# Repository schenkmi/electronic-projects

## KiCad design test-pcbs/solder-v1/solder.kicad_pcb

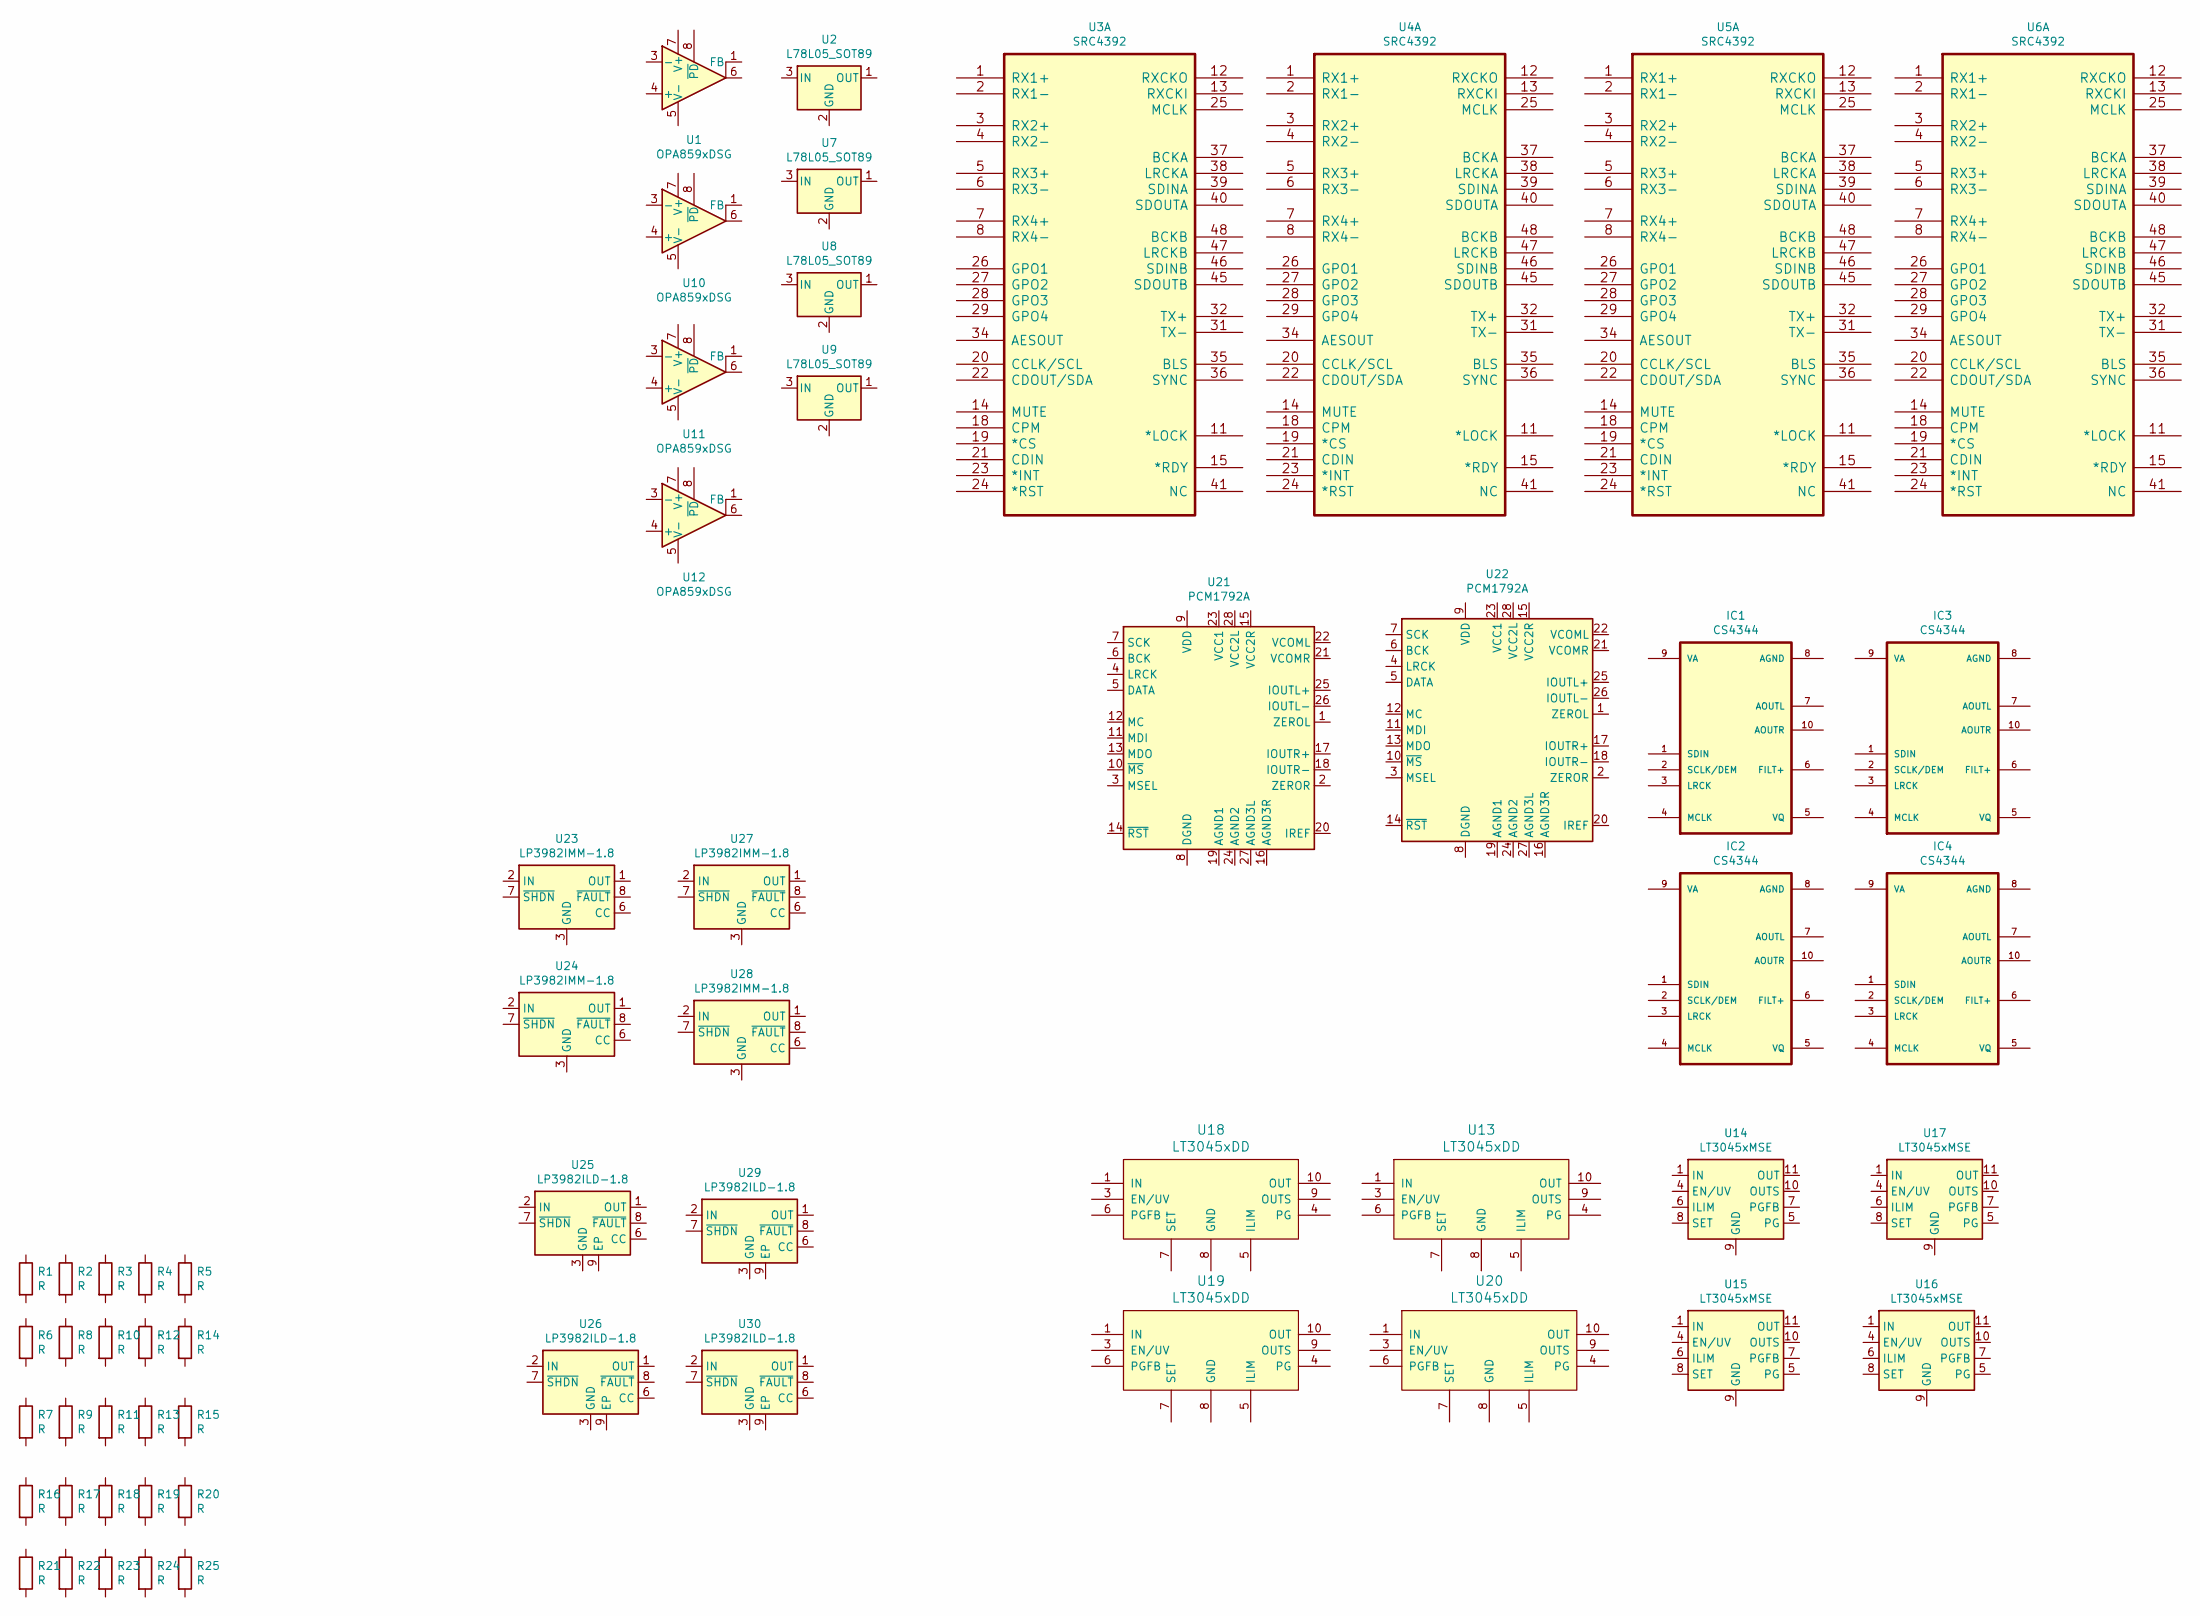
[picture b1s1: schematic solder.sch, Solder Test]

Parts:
IC1, IC2, IC3, IC4: CS4344; TSSOP-10_3x3mm_P0.5mm; MPN CS4344-DZZ
R1, R2, R3, R4, R5: R; R_0805_2012Metric_Pad1.20x1.40mm_HandSolder
R6, R8, R10, R12, R14: R; R_0603_1608Metric_Pad0.98x0.95mm_HandSolder
R7, R9, R11, R13, R15: R; R_0603_1608Metric
R16, R17, R18, R19, R20: R; R_0402_1005Metric_Pad0.72x0.64mm_HandSolder
R21, R22, R23, R24, R25: R; R_0402_1005Metric
U1, U10, U11, U12: OPA859xDSG; WSON-8-1EP_2x2mm_P0.5mm_EP0.9x1.6mm
U2, U7, U8, U9: L78L05_SOT89; SOT-89-3
U3, U4, U5, U6: SRC4392; TQFP-48_7x7mm_P0.5mm
U13, U18, U19, U20: LT3045xDD; DFN-10-1EP_3x3mm_P0.5mm_EP1.55x2.48mm
U14, U15, U16, U17: LT3045xMSE; MSOP-12-1EP_3x4mm_P0.65mm_EP1.65x2.85mm
U21, U22: PCM1792A; SSOP-28_5.3x10.2mm_P0.65mm
U23, U24, U27, U28: LP3982IMM-1.8; VSSOP-8_3.0x3.0mm_P0.65mm
U25, U26, U29, U30: LP3982ILD-1.8; WSON-8-1EP_3x2.5mm_P0.5mm_EP1.2x1.5mm_PullBack_ThermalVias

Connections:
unnamed: U1.5 (V-), U1.9 (V-)
unnamed: U10.5 (V-), U10.9 (V-)
unnamed: U11.5 (V-), U11.9 (V-)
unnamed: U12.5 (V-), U12.9 (V-)
unnamed: U13.1 (IN), U13.2 (IN)
unnamed: U13.8 (GND), U13.11 (GND)
unnamed: U14.1 (IN), U14.2 (IN), U14.3 (IN)
unnamed: U14.11 (OUT), U14.12 (OUT)
unnamed: U14.9 (GND), U14.13 (GND)
unnamed: U15.1 (IN), U15.2 (IN), U15.3 (IN)
unnamed: U15.11 (OUT), U15.12 (OUT)
unnamed: U15.9 (GND), U15.13 (GND)
unnamed: U16.1 (IN), U16.2 (IN), U16.3 (IN)
unnamed: U16.11 (OUT), U16.12 (OUT)
unnamed: U16.9 (GND), U16.13 (GND)
unnamed: U17.1 (IN), U17.2 (IN), U17.3 (IN)
unnamed: U17.11 (OUT), U17.12 (OUT)
unnamed: U17.9 (GND), U17.13 (GND)
unnamed: U18.1 (IN), U18.2 (IN)
unnamed: U18.8 (GND), U18.11 (GND)
unnamed: U19.1 (IN), U19.2 (IN)
unnamed: U19.8 (GND), U19.11 (GND)
unnamed: U20.1 (IN), U20.2 (IN)
unnamed: U20.8 (GND), U20.11 (GND)
unnamed: U23.1 (OUT), U23.4 (OUT)
unnamed: U24.1 (OUT), U24.4 (OUT)
unnamed: U25.1 (OUT), U25.4 (OUT)
unnamed: U26.1 (OUT), U26.4 (OUT)
unnamed: U27.1 (OUT), U27.4 (OUT)
unnamed: U28.1 (OUT), U28.4 (OUT)
unnamed: U29.1 (OUT), U29.4 (OUT)
unnamed: U30.1 (OUT), U30.4 (OUT)

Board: 2 copper layers, 59 parts (0 on the bottom side), 32 nets, no tracks yet.

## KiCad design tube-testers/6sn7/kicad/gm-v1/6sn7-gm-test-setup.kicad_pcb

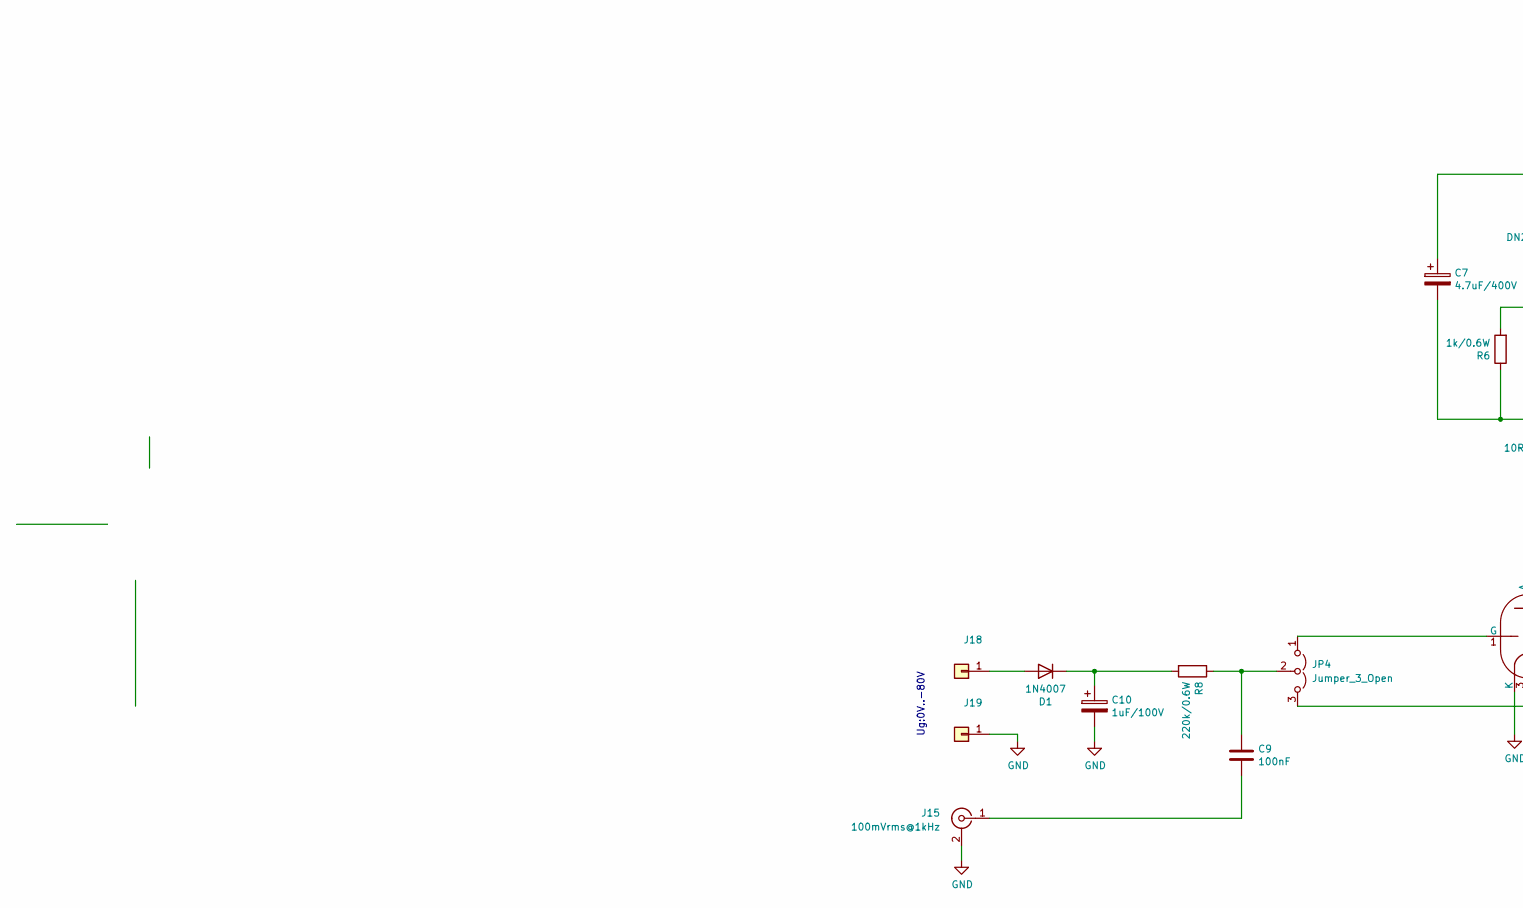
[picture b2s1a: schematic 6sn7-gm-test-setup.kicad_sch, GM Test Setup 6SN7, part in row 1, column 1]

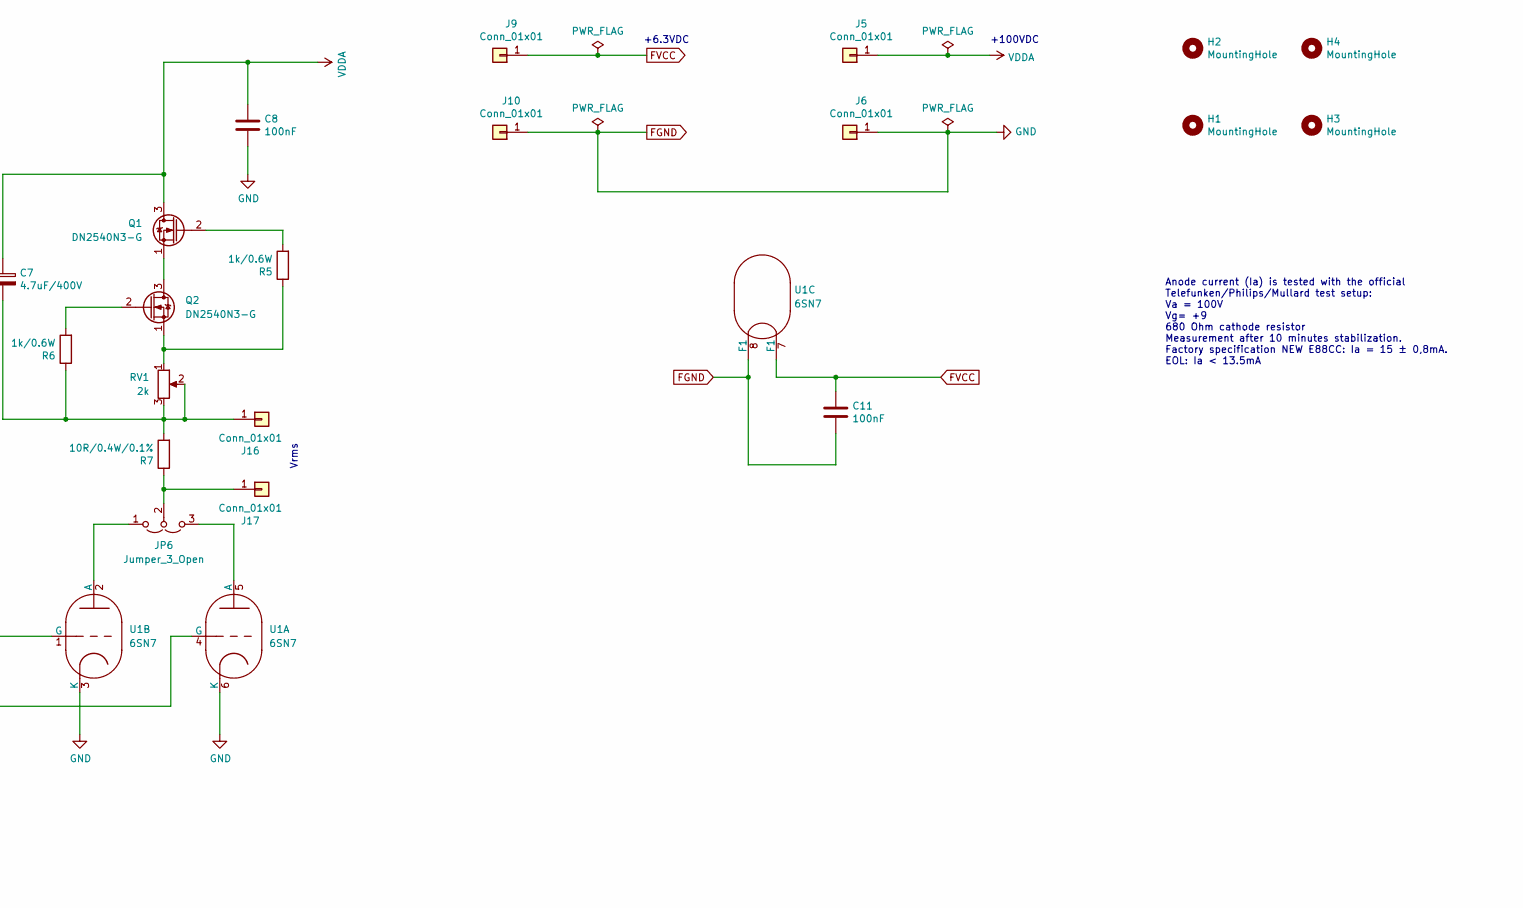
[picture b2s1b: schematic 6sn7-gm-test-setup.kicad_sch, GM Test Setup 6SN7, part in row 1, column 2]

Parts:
C7: 4.7uF/400V; CP_Radial_D10.0mm_P5.00mm
C8: 100nF; C_Rect_L16.5mm_W5.0mm_P15.00mm_MKT
C9, C11: 100nF; C_Rect_L7.2mm_W2.5mm_P5.00mm_FKS2_FKP2_MKS2_MKP2
C10: 1uF/100V; CP_Radial_D5.0mm_P2.00mm
D1: 1N4007; D_DO-41_SOD81_P10.16mm_Horizontal
H1, H2, H3, H4: MountingHole; MountingHole_3.2mm_M3_Pad_Via
J5, J6, J9, J10: Conn_01x01; Pin_D1.3mm_L11.0mm
J15: 100mVrms@1kHz; RCA-Phono_CUI-Devices_RCJ-02X_Vertical
J16, J17: Conn_01x01; Pin_D1.0mm_L10.0mm
J18, J19: Pin_D1.0mm_L10.0mm
JP4, JP6: Jumper_3_Open; PinHeader_1x03_P2.54mm_Vertical
Q1, Q2: DN2540N3-G; TO-92_Inline
R5, R6: 1k/0.6W; R_Axial_DIN0207_L6.3mm_D2.5mm_P10.16mm_Horizontal
R7: 10R/0.4W/0.1%; R_Axial_DIN0207_L6.3mm_D2.5mm_P10.16mm_Horizontal
R8: 220k/0.6W; R_Axial_DIN0207_L6.3mm_D2.5mm_P10.16mm_Horizontal
RV1: 2k; Potentiometer_Bourns_3296W_Vertical
U1: 6SN7; TubeOctal

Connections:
FGND: C8.2, C10.2, C11.2, J6.1, J10.1, J15.2 (Ext), J19.1, U1.3 (K), U1.6 (K), U1.8 (F1)
FVCC: C11.1, J9.1, U1.7 (F1)
unnamed: D1.2 (A), J18.1
unnamed: C10.1, D1.1 (K), R8.2
unnamed: C9.2, J15.1 (In)
unnamed: C7.2, J16.1, R6.1, R7.2, RV1.2, RV1.3
unnamed: J17.1, JP6.2 (C), R7.1
unnamed: JP4.1 (A), U1.1 (G)
unnamed: JP4.3 (B), U1.4 (G)
unnamed: C9.1, JP4.2 (C), R8.1
unnamed: JP6.1 (A), U1.2 (A)
unnamed: JP6.3 (B), U1.5 (A)
unnamed: Q1.2 (G), R5.2
unnamed: Q1.1 (S), Q2.3 (D)
unnamed: Q2.2 (G), R6.2
unnamed: Q2.1 (S), R5.1, RV1.1
VDDA: C7.1, C8.1, J5.1, Q1.3 (D)

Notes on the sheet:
+6.3VDC
Anode current (Ia) is tested with the official Telefunken/Philips/Mullard test setup: Va = 100V Vg= +9 680 Ohm cathode resistor Measurement after 10 minutes stabilization. Factory specification NEW E88CC: Ia = 15 ± 0,8mA. EOL: Ia < 13.5mA
+100VDC
Vrms
Ug:0V..-80V

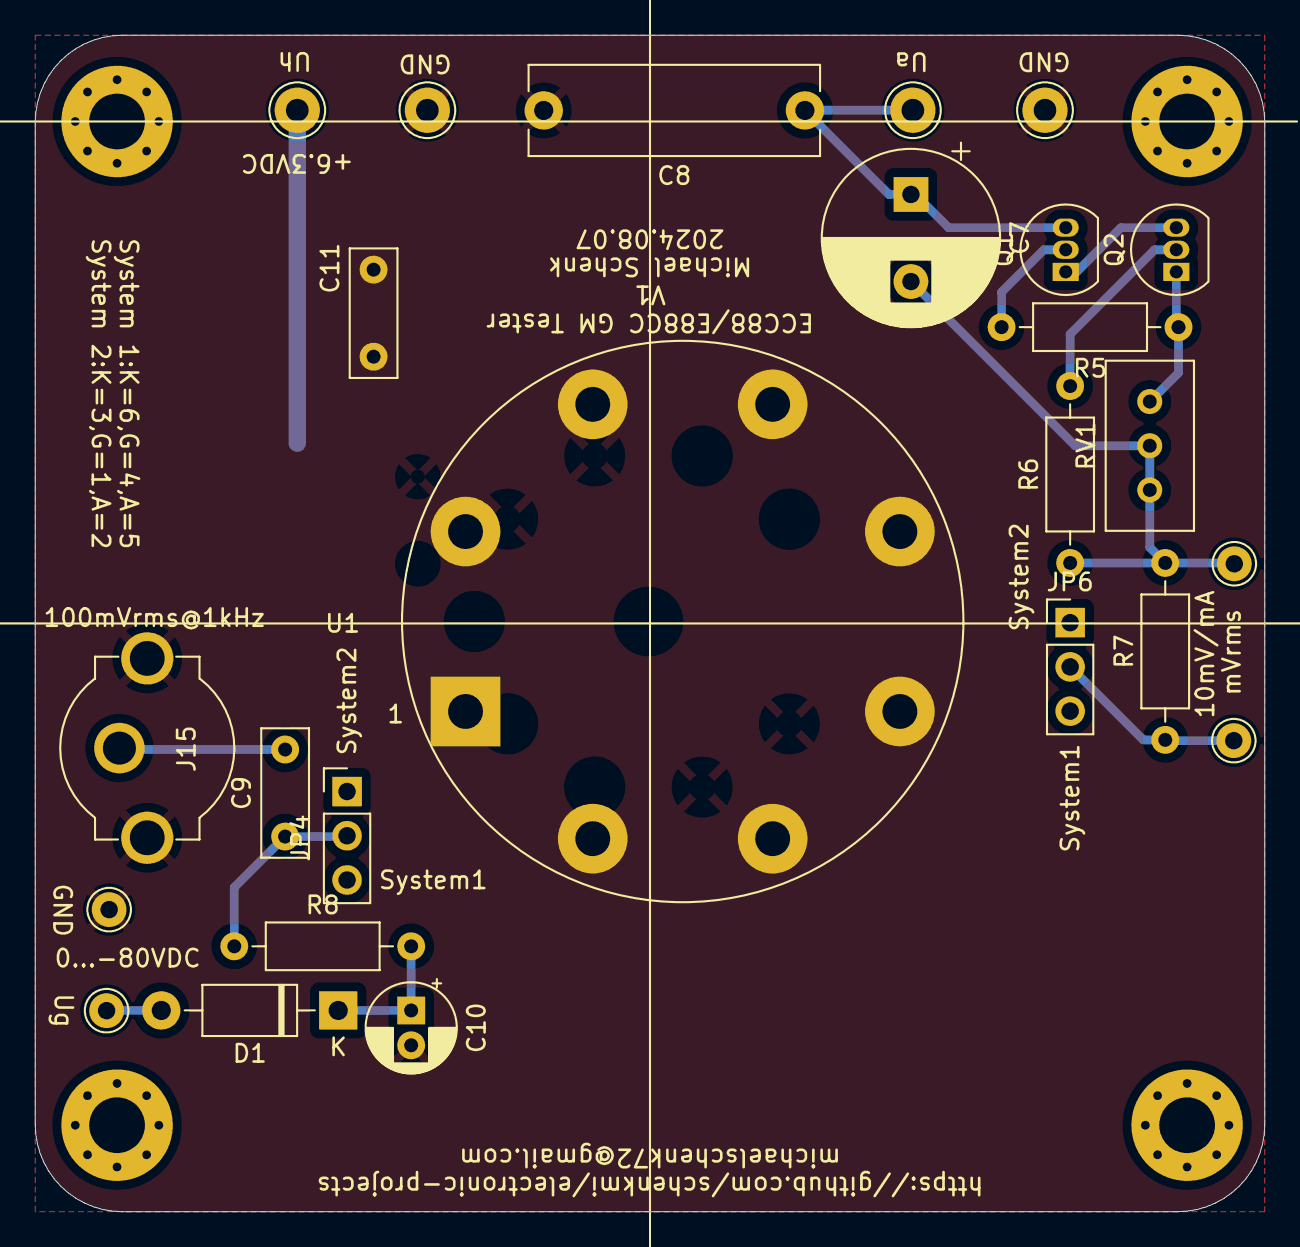
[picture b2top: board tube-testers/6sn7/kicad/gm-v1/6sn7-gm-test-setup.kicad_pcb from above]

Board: 2 copper layers, 70.6 x 67.6 mm, 29 parts (0 on the bottom side), 17 nets.

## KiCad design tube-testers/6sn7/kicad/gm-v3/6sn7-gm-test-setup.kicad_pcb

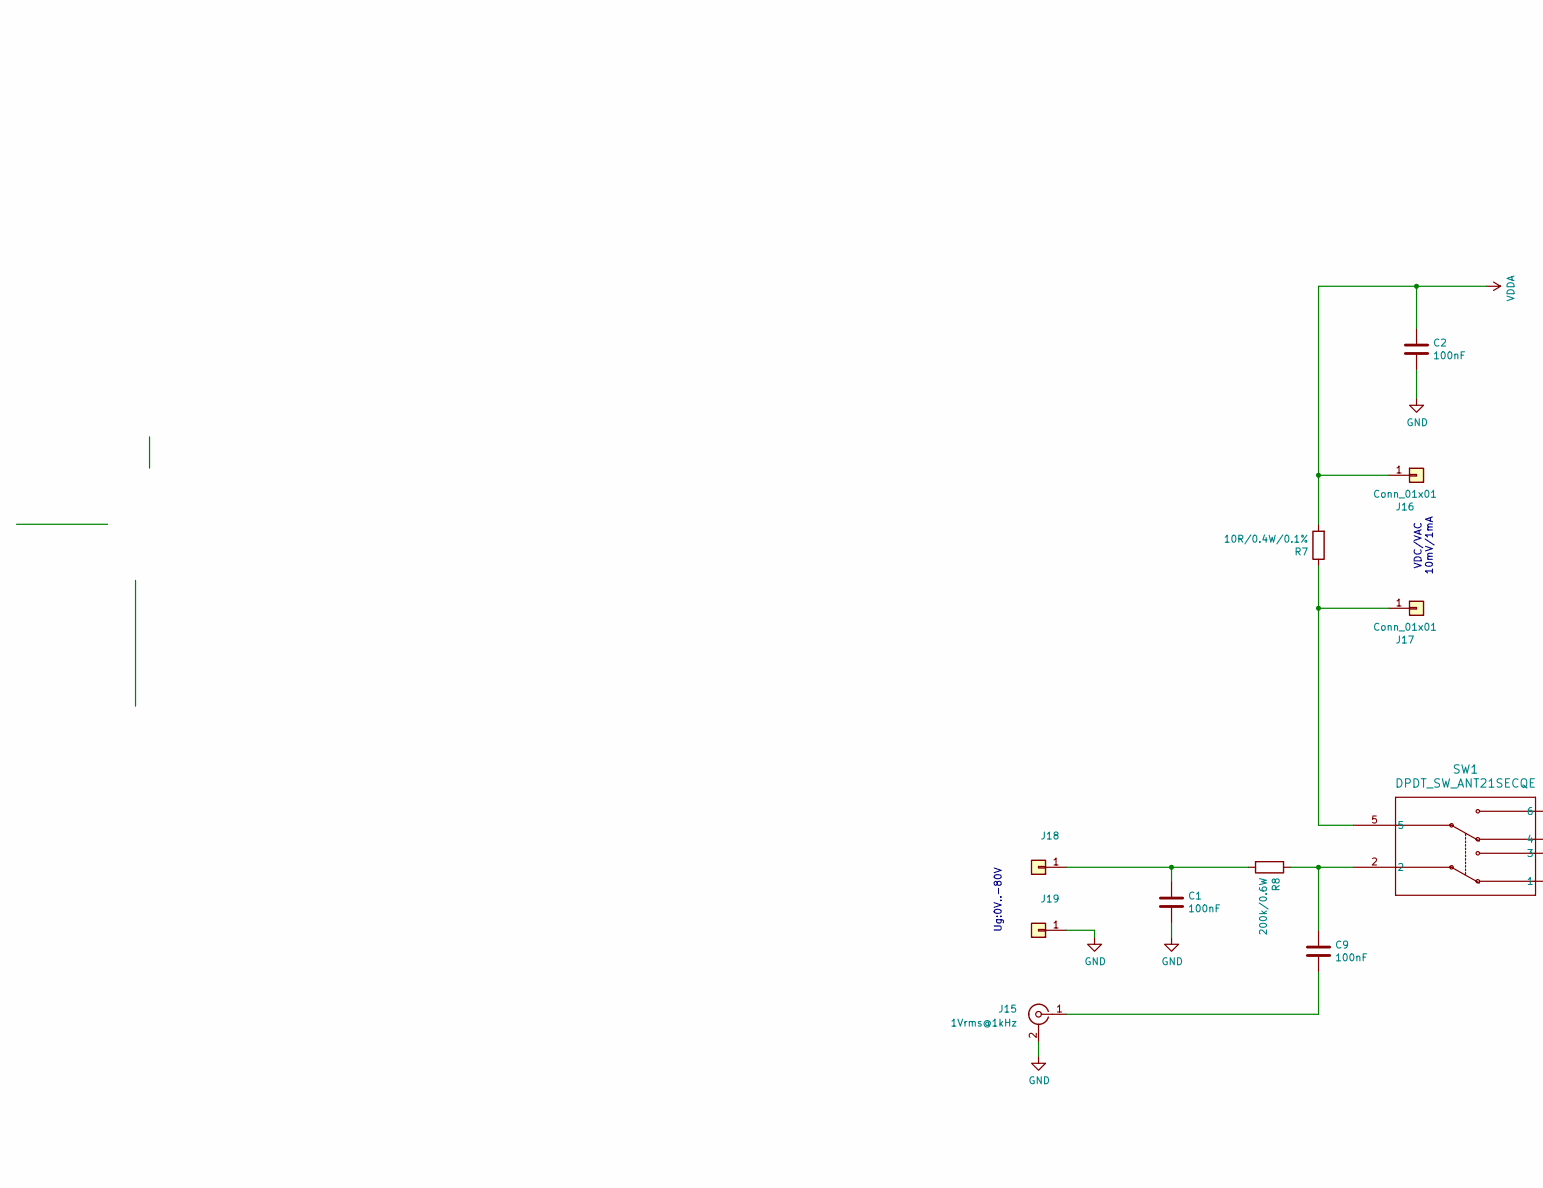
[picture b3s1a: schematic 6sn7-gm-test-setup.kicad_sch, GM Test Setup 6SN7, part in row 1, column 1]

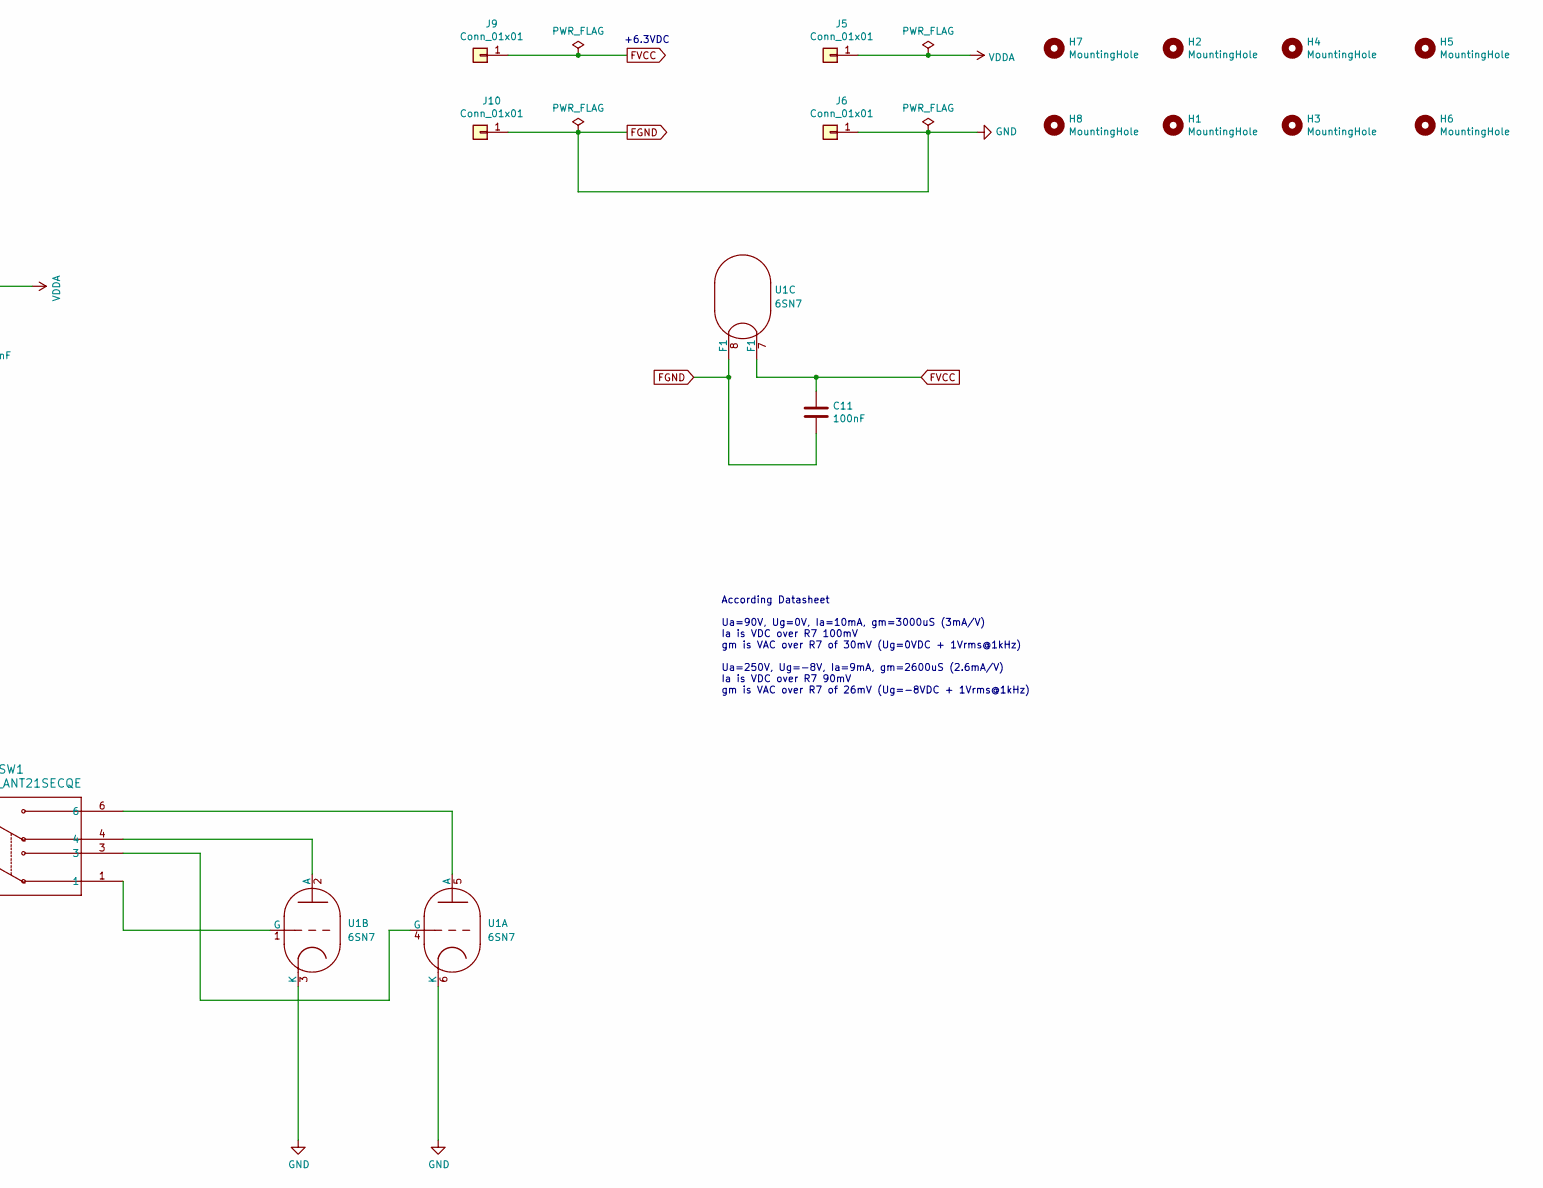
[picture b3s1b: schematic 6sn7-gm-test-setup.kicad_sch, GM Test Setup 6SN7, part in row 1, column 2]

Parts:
C1, C9, C11: 100nF; C_Rect_L7.2mm_W2.5mm_P5.00mm_FKS2_FKP2_MKS2_MKP2
C2: 100nF; C_Rect_L16.5mm_W5.0mm_P15.00mm_MKT
H1, H2, H3, H4, H5, H6, H7, H8: MountingHole; MountingHole_3.2mm_M3_Pad_Via
J5, J6, J9, J10: Conn_01x01; Pin_D1.3mm_L11.0mm
J15: 1Vrms@1kHz; RCA-Phono_CUI-Devices_RCJ-02X_Vertical
J16, J17: Conn_01x01; Pin_D1.0mm_L10.0mm
J18, J19: Pin_D1.0mm_L10.0mm
R7: 10R/0.4W/0.1%; R_Axial_DIN0207_L6.3mm_D2.5mm_P10.16mm_Horizontal
R8: 200k/0.6W; R_Axial_DIN0207_L6.3mm_D2.5mm_P10.16mm_Horizontal
SW1: DPDT_SW_ANT21SECQE; SW6_ANT21SECQE_CRS
U1: 6SN7; TubeOctal

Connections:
FGND: C1.2, C2.2, C11.2, J6.1, J10.1, J15.2 (Ext), J19.1, U1.3 (K), U1.6 (K), U1.8 (F1)
FVCC: C11.1, J9.1, U1.7 (F1)
unnamed: C9.1, R8.1, SW1.2
unnamed: C9.2, J15.1 (In)
unnamed: J17.1, R7.1, SW1.5
unnamed: C1.1, J18.1, R8.2
unnamed: SW1.6, U1.5 (A)
unnamed: SW1.3, U1.4 (G)
unnamed: SW1.4, U1.2 (A)
unnamed: SW1.1, U1.1 (G)
VDDA: C2.1, J5.1, J16.1, R7.2

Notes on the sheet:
+6.3VDC
VDC/VAC 10mV/1mA
Ug:0V..-80V
According Datasheet Ua=90V, Ug=0V, Ia=10mA, gm=3000uS (3mA/V) Ia is VDC over R7 100mV gm is VAC over R7 of 30mV (Ug=0VDC + 1Vrms@1kHz) Ua=250V, Ug=-8V, Ia=9mA, gm=2600uS (2.6mA/V) Ia is VDC over R7 90mV gm is VAC over R7 of 26mV (Ug=-8VDC + 1Vrms@1kHz)

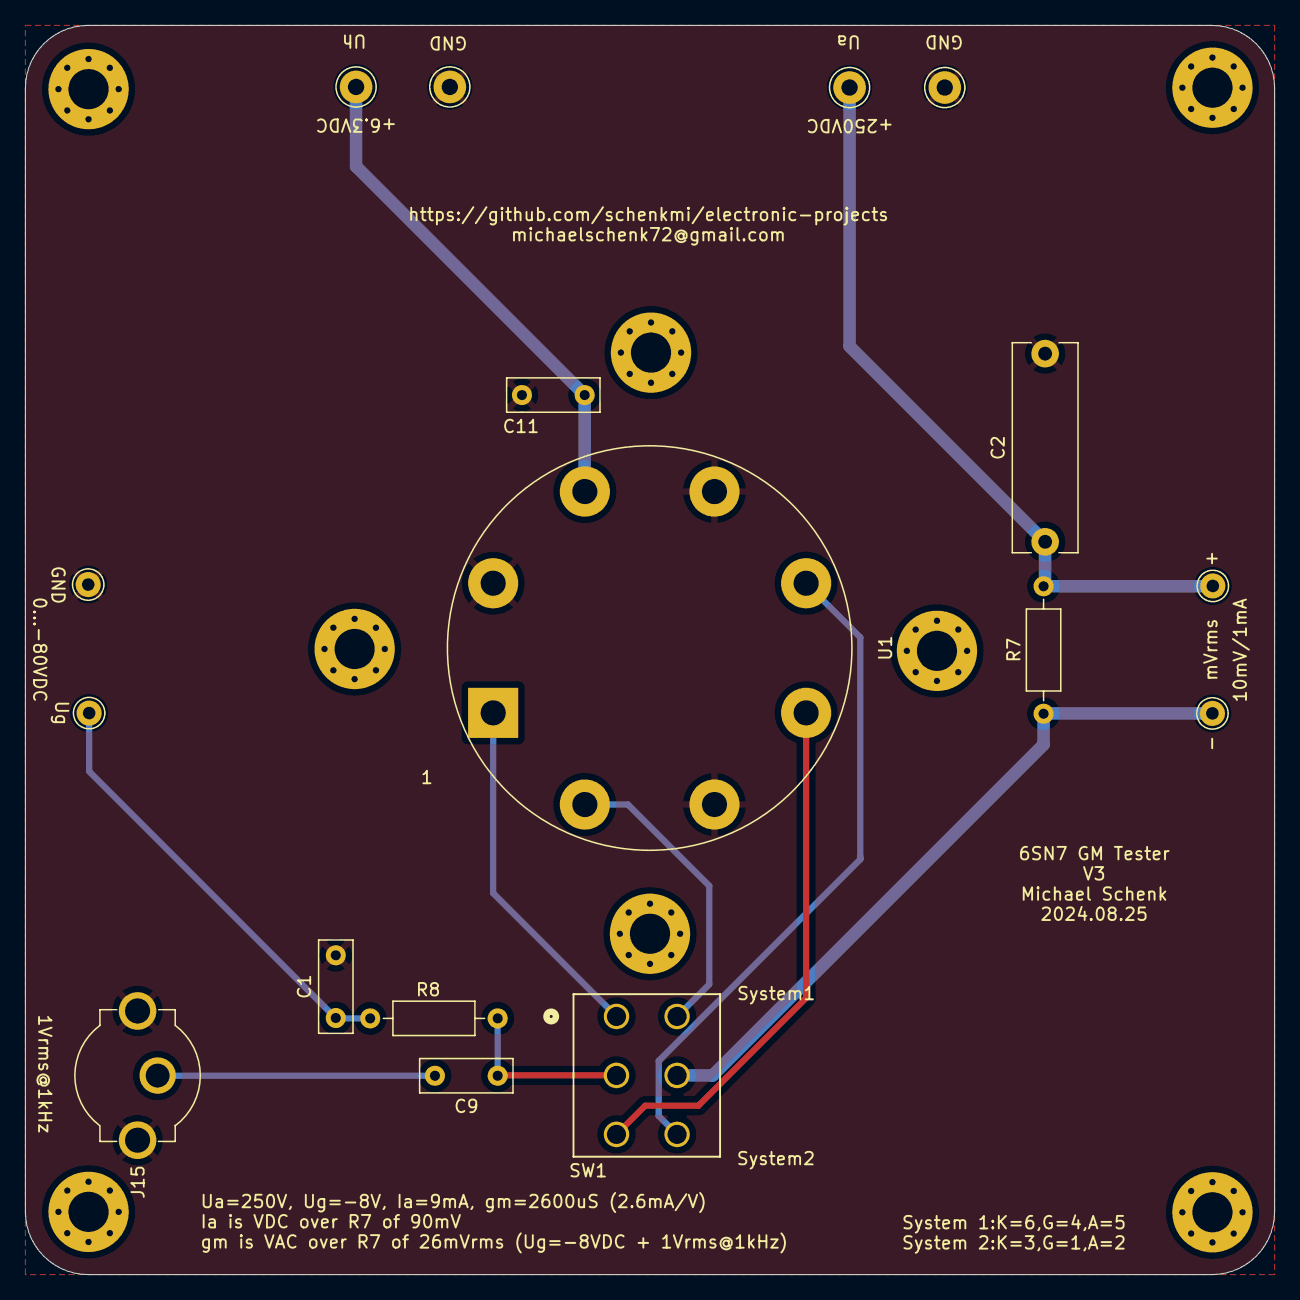
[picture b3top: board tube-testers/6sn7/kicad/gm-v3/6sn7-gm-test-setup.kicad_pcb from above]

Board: 2 copper layers, 99.6 x 99.6 mm, 25 parts (0 on the bottom side), 11 nets.

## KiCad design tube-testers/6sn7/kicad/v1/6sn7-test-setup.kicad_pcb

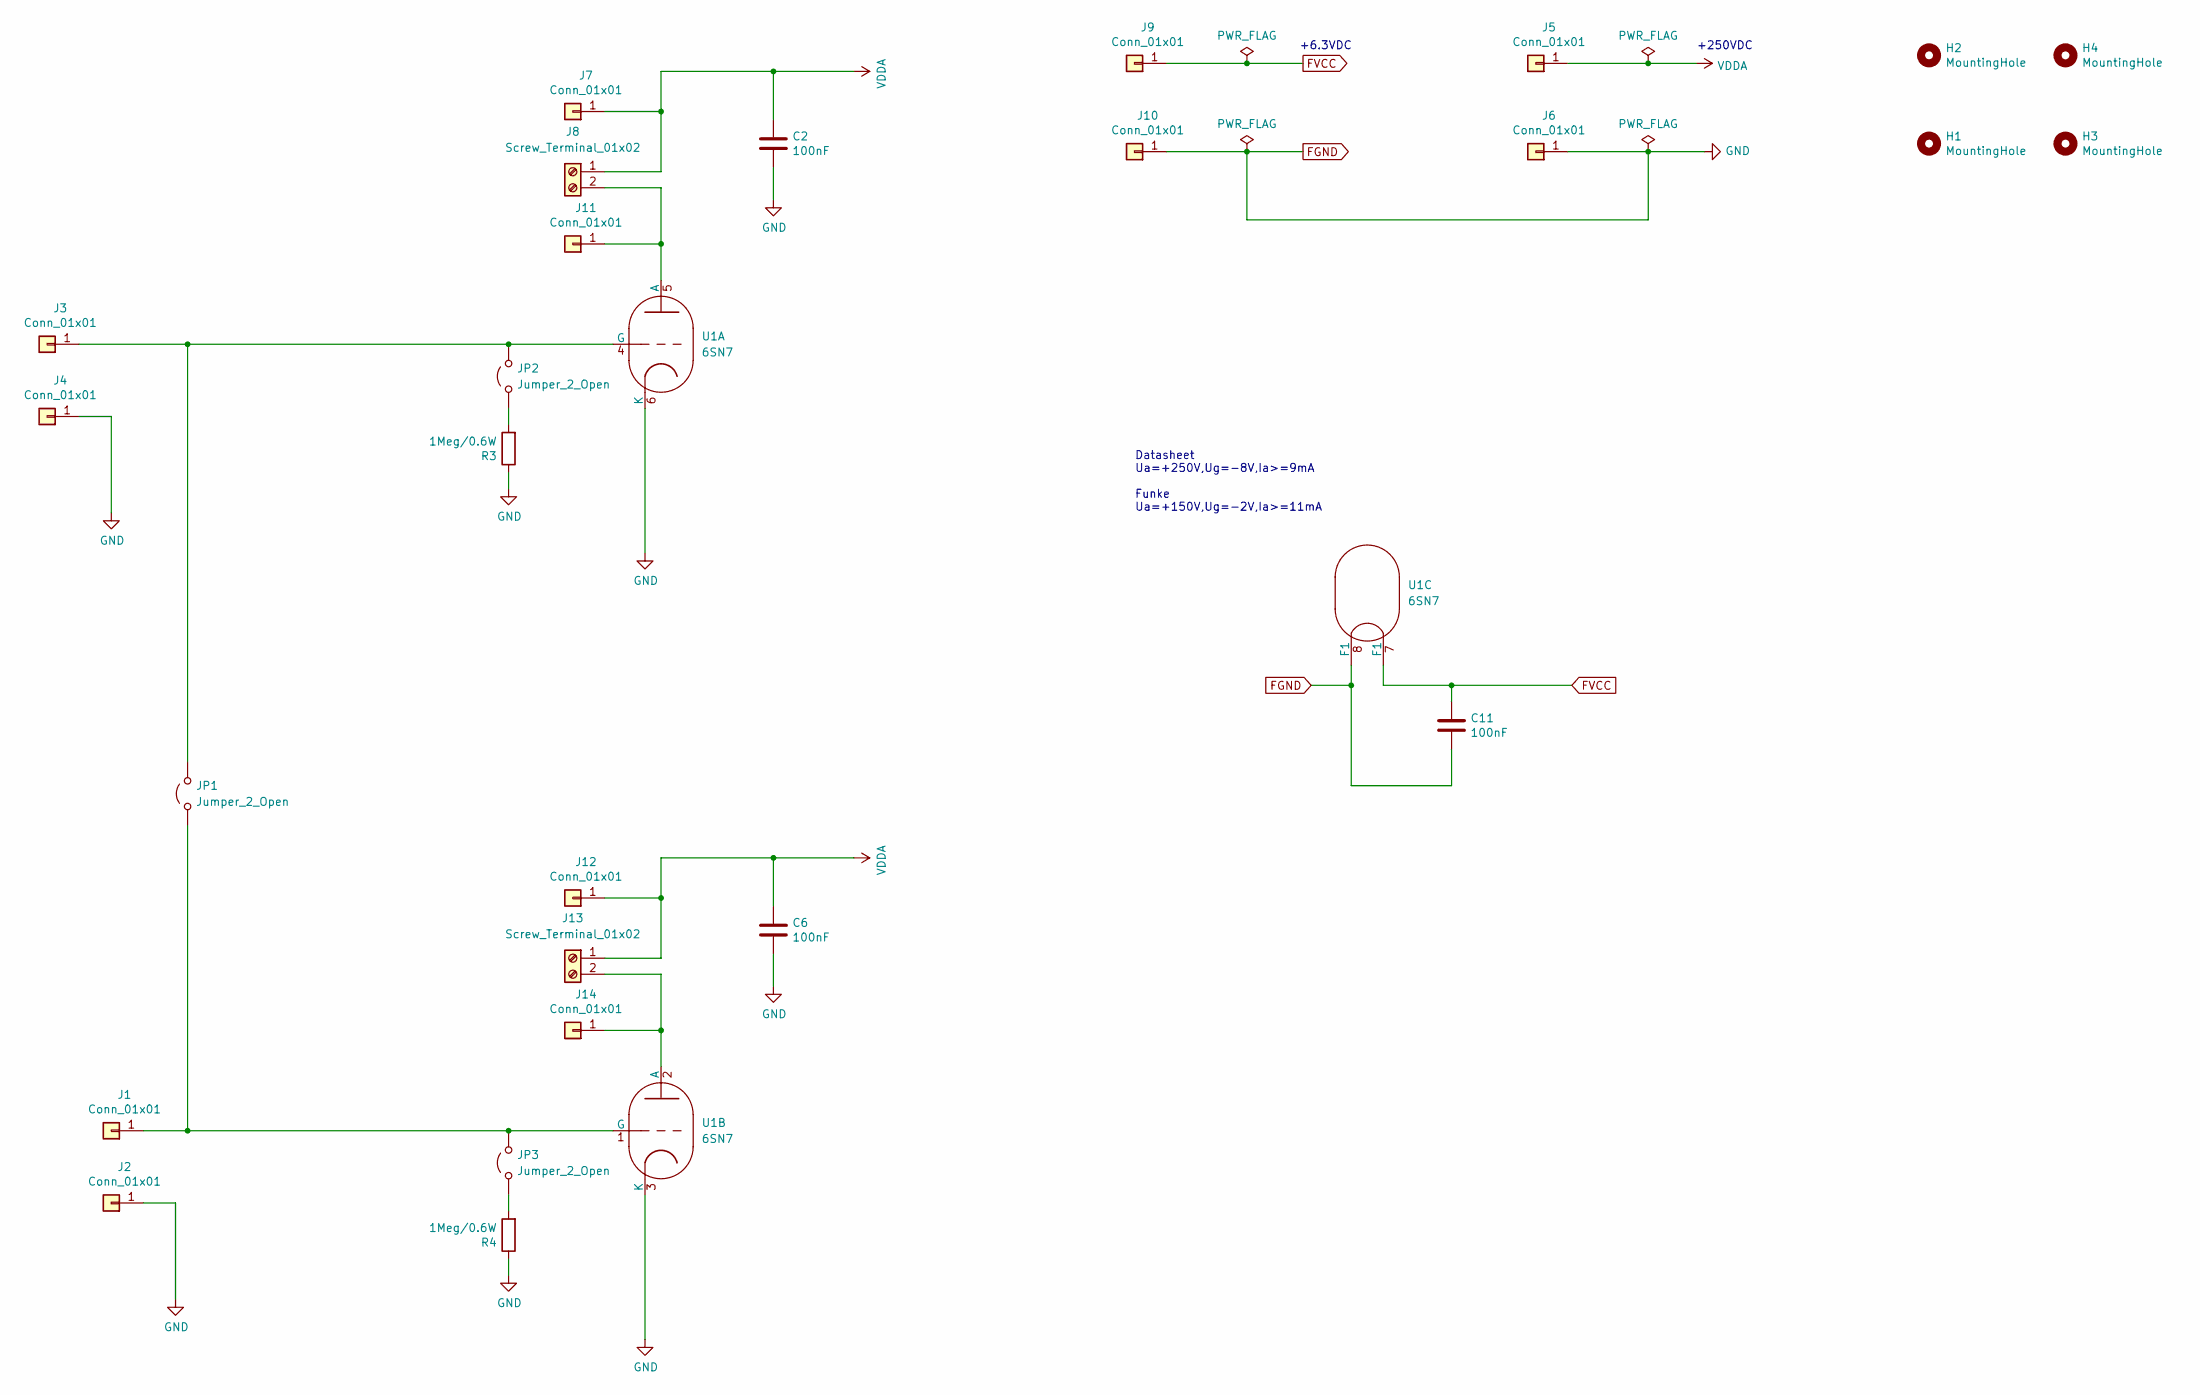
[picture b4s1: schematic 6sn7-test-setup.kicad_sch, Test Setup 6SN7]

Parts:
C2, C6: 100nF; C_Rect_L16.5mm_W5.0mm_P15.00mm_MKT
C11: 100nF; C_Rect_L7.2mm_W2.5mm_P5.00mm_FKS2_FKP2_MKS2_MKP2
H1, H2, H3, H4: MountingHole; MountingHole_3.2mm_M3_Pad_Via
J1, J2, J3, J4, J7, J11, J12, J14: Conn_01x01; Pin_D1.0mm_L10.0mm
J5, J6, J9, J10: Conn_01x01; Pin_D1.3mm_L11.0mm
J8, J13: Screw_Terminal_01x02; TerminalBlock_RND_205-00012_1x02_P5.00mm_Horizontal
JP1, JP2, JP3: Jumper_2_Open; PinHeader_1x02_P2.54mm_Vertical
R3, R4: 1Meg/0.6W; R_Axial_DIN0207_L6.3mm_D2.5mm_P10.16mm_Horizontal
U1: 6SN7; TubeOctal

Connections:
FGND: C2.2, C6.2, C11.2, J2.1, J4.1, J6.1, J10.1, R3.1, R4.1, U1.3 (K), U1.6 (K), U1.8 (F1)
FVCC: C11.1, J9.1, U1.7 (F1)
unnamed: J1.1, JP1.1 (A), JP3.2 (B), U1.1 (G)
unnamed: J3.1, JP1.2 (B), JP2.2 (B), U1.4 (G)
unnamed: J8.2, J11.1, U1.5 (A)
unnamed: J13.2, J14.1, U1.2 (A)
unnamed: JP2.1 (A), R3.2
unnamed: JP3.1 (A), R4.2
VDDA: C2.1, C6.1, J5.1, J7.1, J8.1, J12.1, J13.1

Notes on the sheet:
+6.3VDC
Datasheet Ua=+250V,Ug=-8V,Ia>=9mA Funke Ua=+150V,Ug=-2V,Ia>=11mA
+250VDC

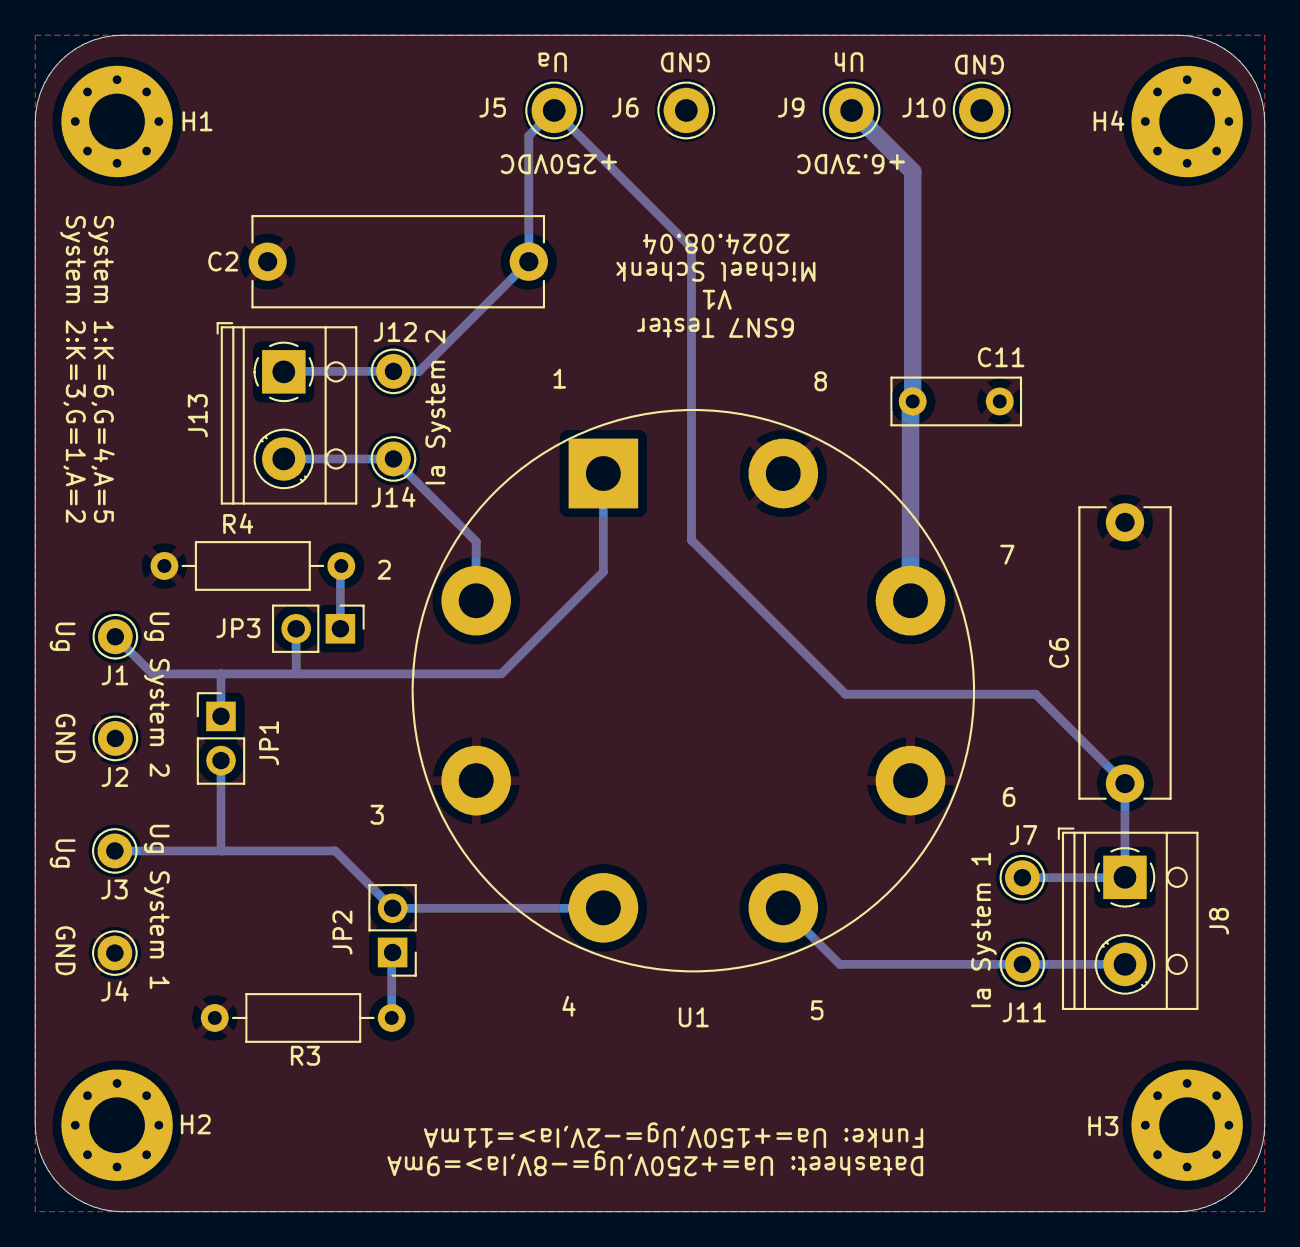
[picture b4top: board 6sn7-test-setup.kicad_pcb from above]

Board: 2 copper layers, 70.6 x 67.6 mm, 27 parts (0 on the bottom side), 9 nets.
